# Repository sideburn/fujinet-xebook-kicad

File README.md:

# FN32ROV XEBook KiCad

A KiCad rebuild of the [FujiNet](https://fujinet.online/) FN32ROV WiFi/SIO adapter for
Atari 8-bit computers, adapted for permanent internal mounting inside an XEBook laptop
build.

This project is derived from the FN32ROV-1.7.1 release in
[FujiNetWIFI/fujinet-hardware](https://github.com/FujiNetWIFI/fujinet-hardware), which is
officially certified open source hardware by [OSHWA](https://oshwa.org) (UID
[US000651](https://certification.oshwa.org/us000651.html)). The original design is in
DipTrace; this project is a from-scratch rebuild in KiCad, since DipTrace's binary file
format has no viable automated conversion path into KiCad and this revision changes
enough of the board that preserving the original layout wasn't a goal.

## Status

Work in progress — schematic and PCB layout are still being built out. Not yet fabricated
or tested.

## What's different from FN32ROV-1.7.1

- The two external Atari SIO connectors (SIO plug + SIO receptacle pass-through) are
  replaced with a single low-profile right-angle 12-pin IDC header, hardwired directly to
  the host motherboard rather than daisy-chaining external SIO peripherals.
- The three status LEDs and three tactile buttons move off the PCB onto JST pigtails, so
  they can be panel-mounted separately from the board.
- The onboard microSD socket is retained, with an added parallel breakout header so the
  card can be relocated to an external board later without a further redesign.

Everything else (ESP32-WROVER-E, CP2102N USB-serial bridge, power path, SIO level
shifters) is carried over from the original design.

## Tooling

Built with KiCad 9. `kicad-cli sch erc` / `kicad-cli pcb drc` are used to verify the
design as it's built.

## License

[CERN Open Hardware Licence Version 2 - Strongly Reciprocal](LICENSE) (CERN-OHL-S-2.0),
matching the copyleft, share-alike spirit of the original OSHWA-certified design.

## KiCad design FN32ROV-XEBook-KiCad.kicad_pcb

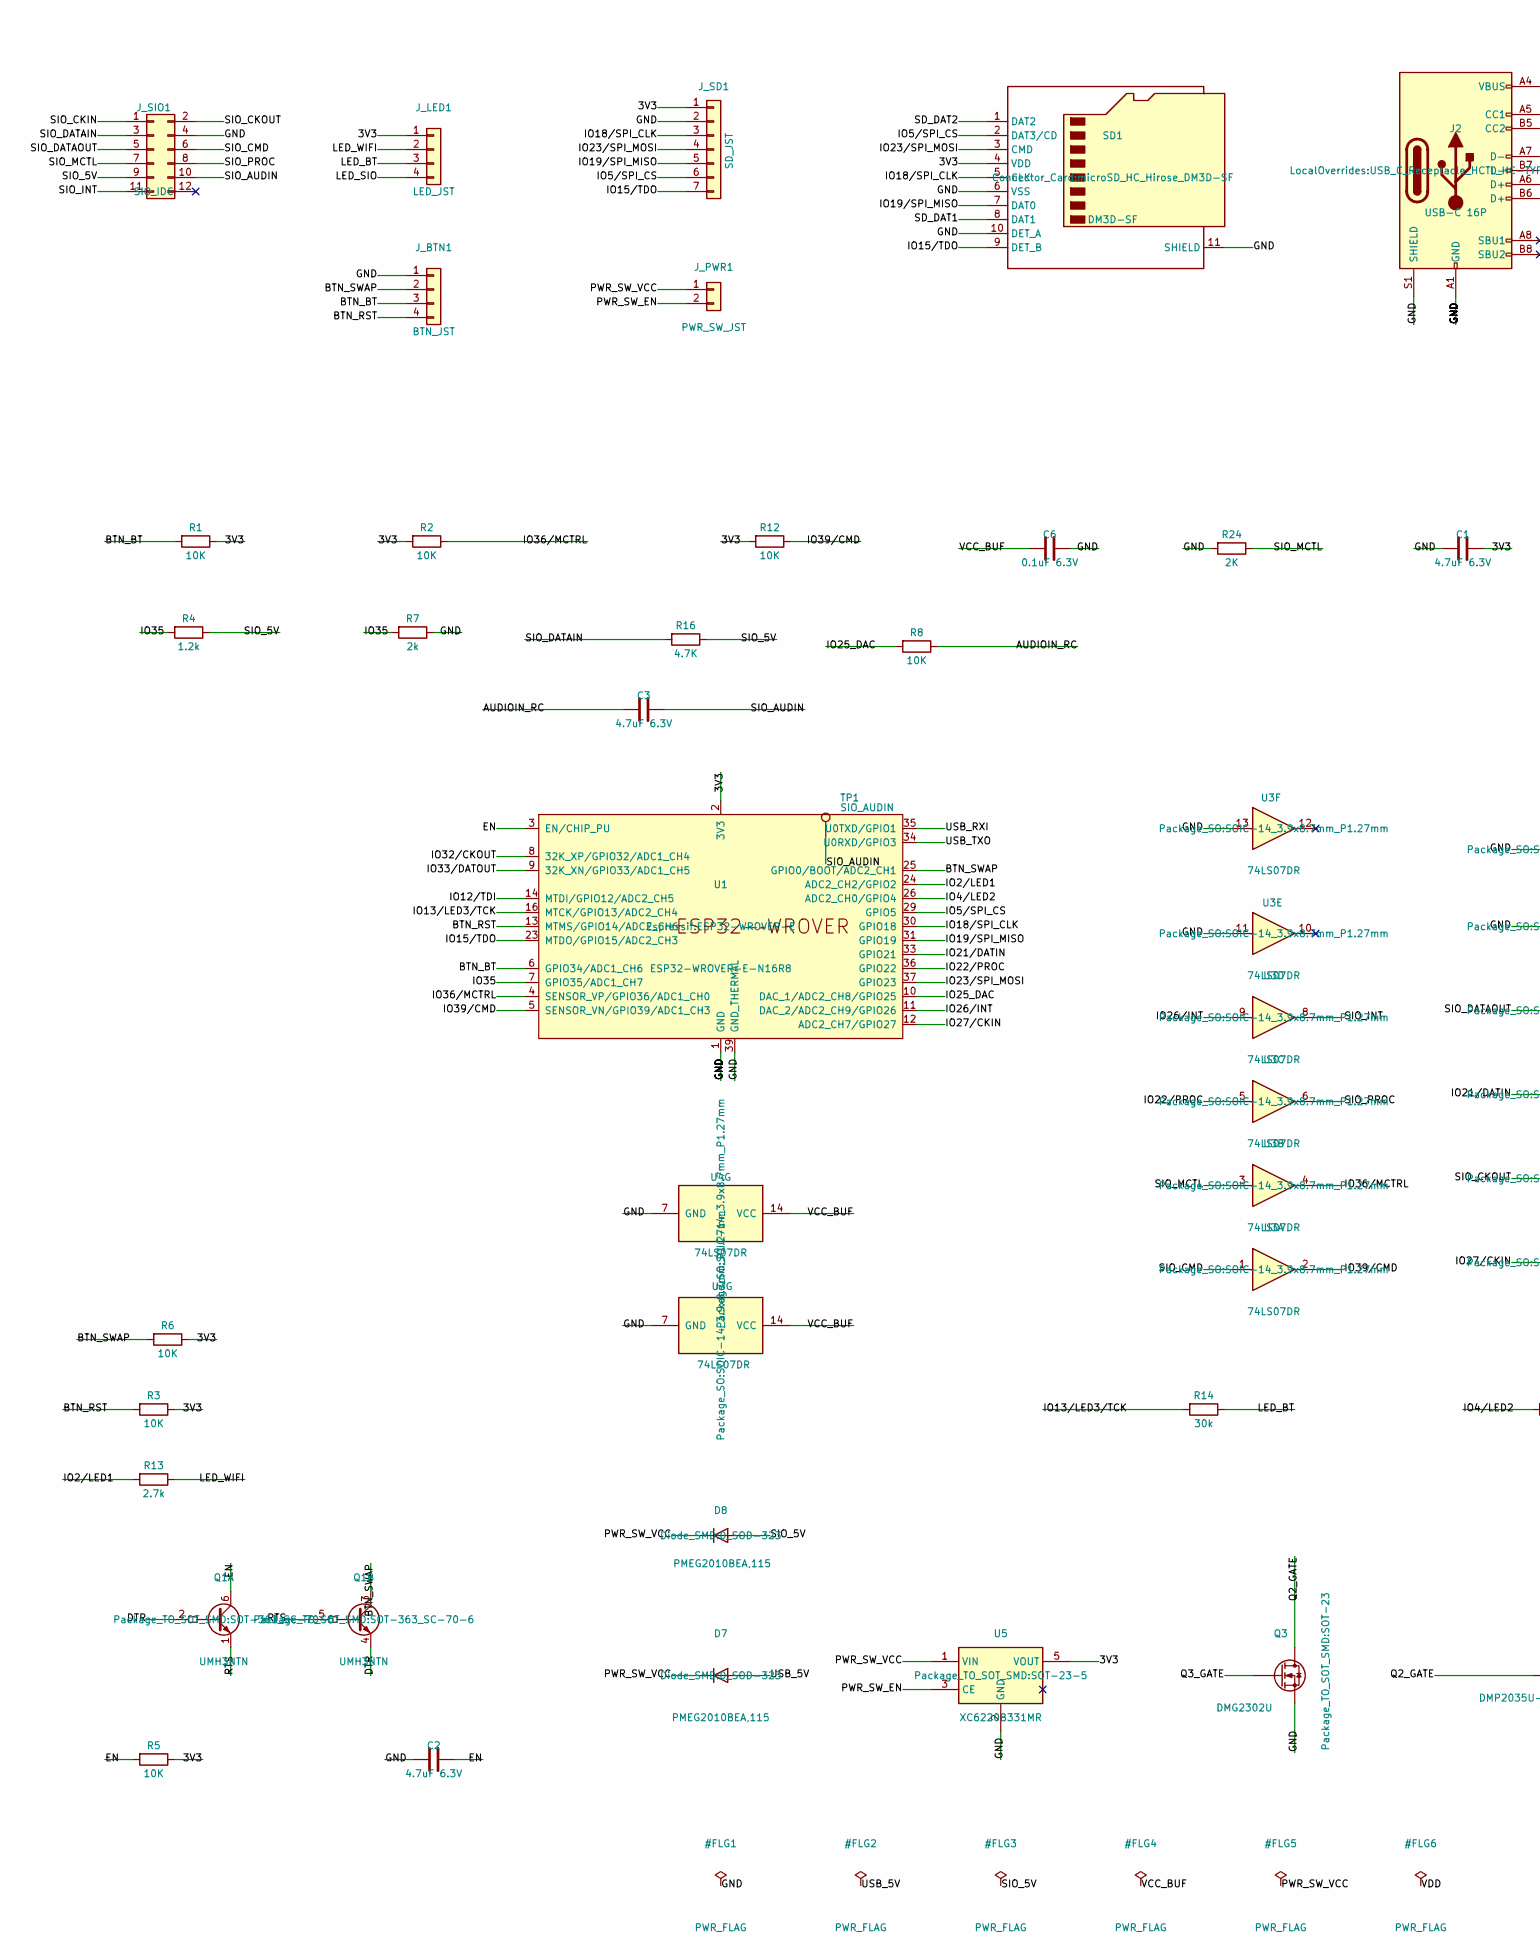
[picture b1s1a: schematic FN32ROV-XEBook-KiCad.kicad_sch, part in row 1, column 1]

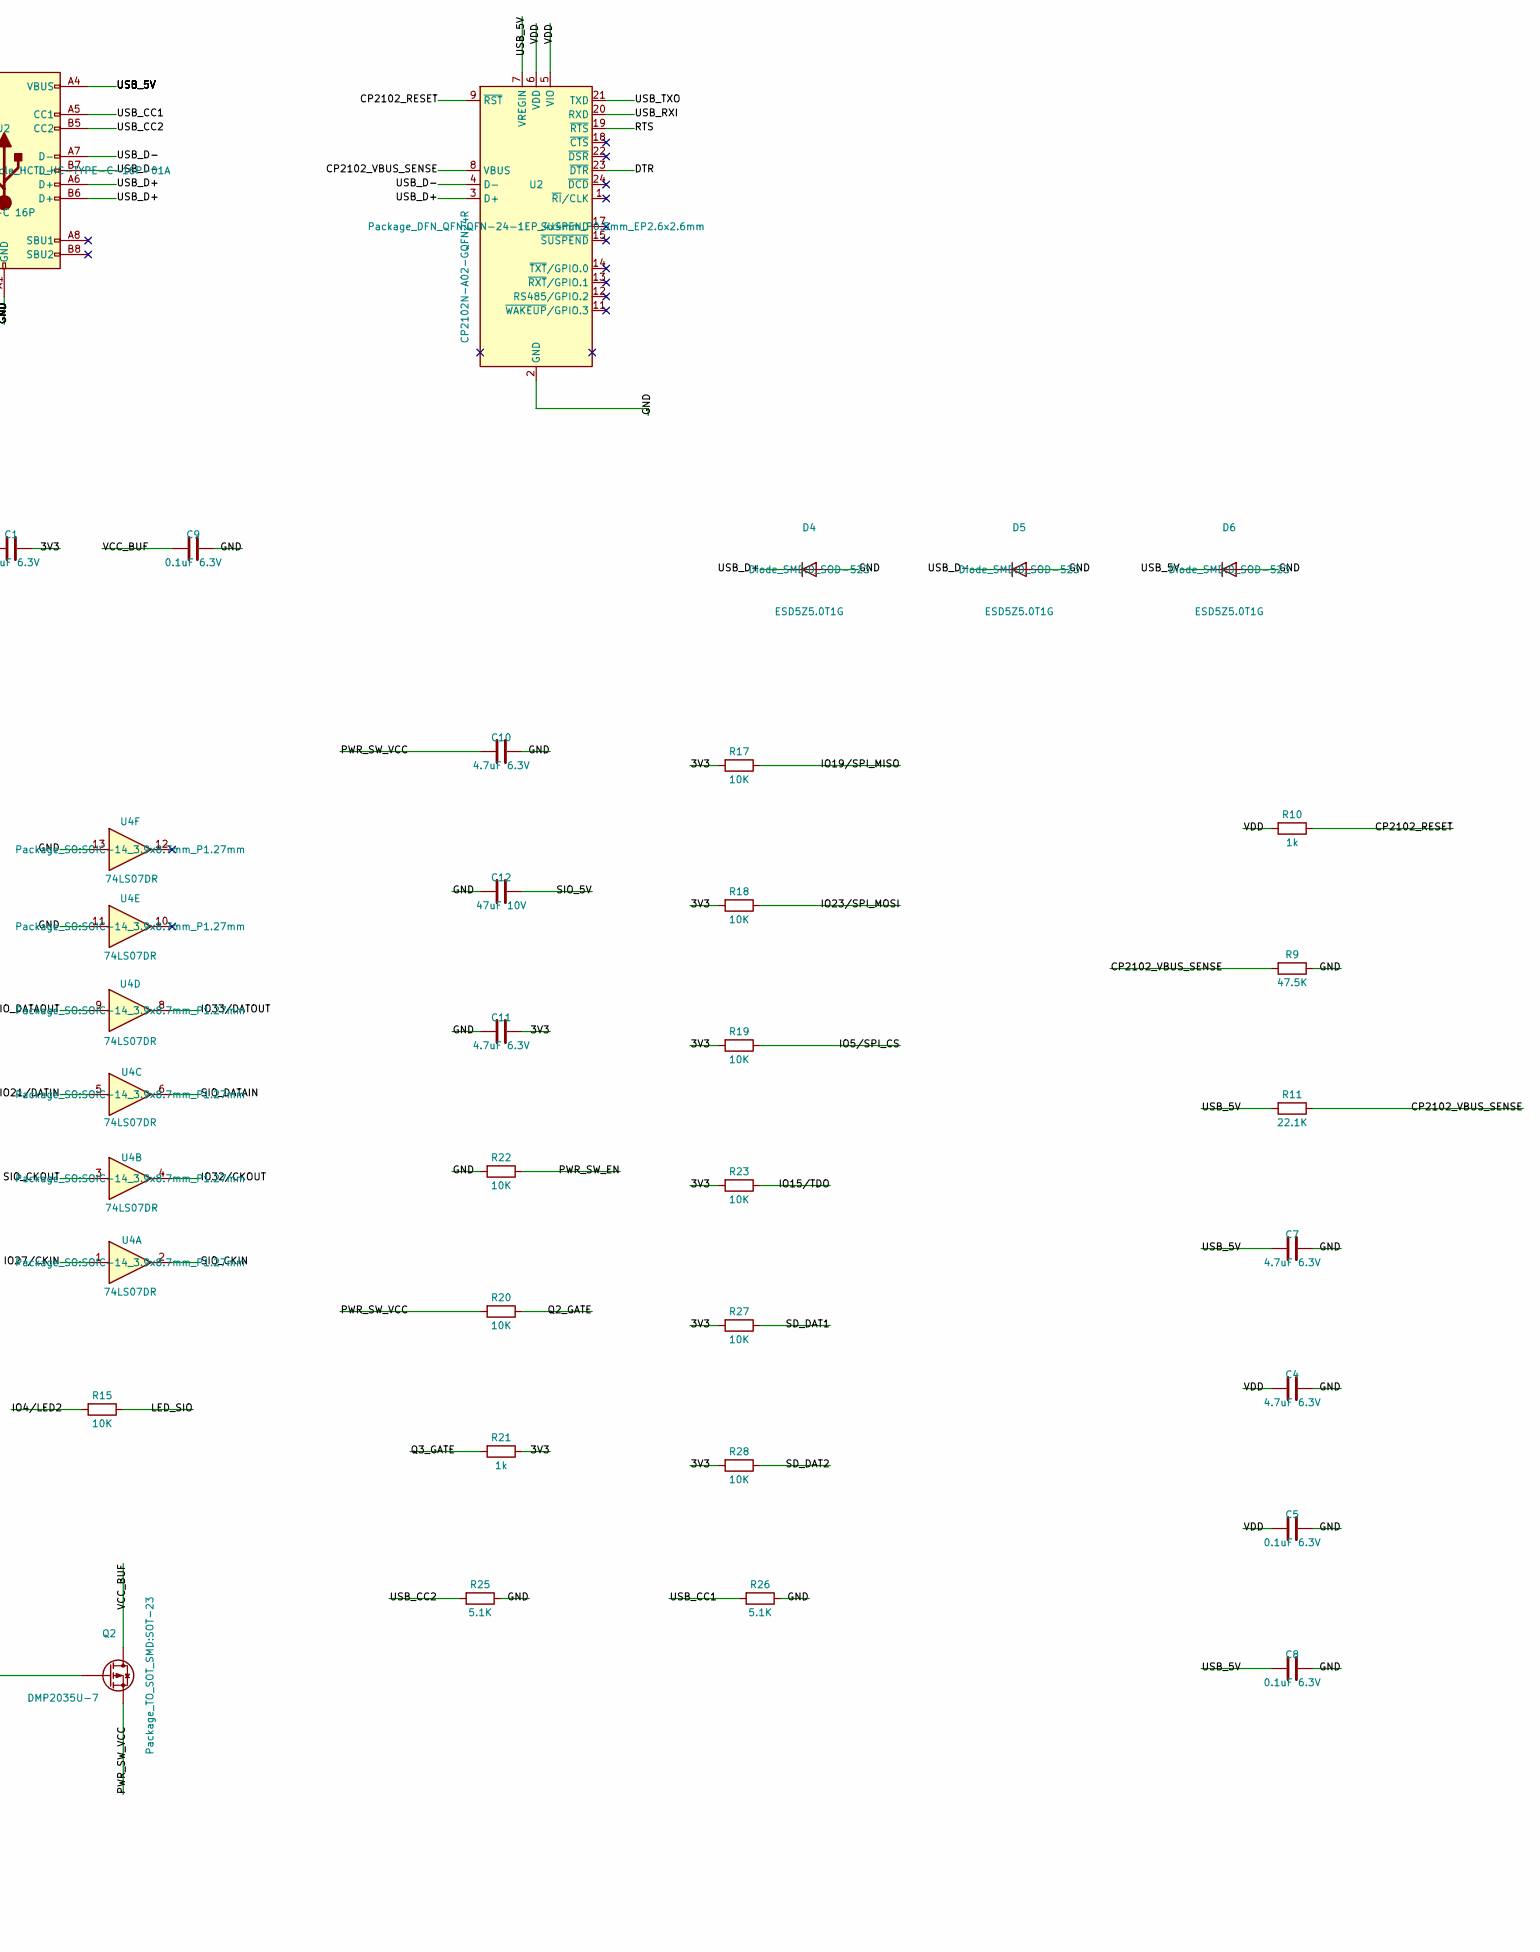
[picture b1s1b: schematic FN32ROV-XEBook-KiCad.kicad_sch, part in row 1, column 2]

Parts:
C1, C2, C3, C4, C7, C10, C11: 4.7uF 6.3V; C_0402_1005Metric
C5, C6, C8, C9: 0.1uF 6.3V; C_0402_1005Metric
C12: 47uF 10V; CP_EIA-7343-31_Kemet-D
D4, D5, D6: ESD5Z5.0T1G; D_SOD-523
D7, D8: PMEG2010BEA,115; D_SOD-323
J2: USB-C 16P; USB_C_Receptacle_HCTL_HC-TYPE-C-16P-01A
J_BTN1: BTN_JST; JST_PH_S4B-PH-K_1x04_P2.00mm_Horizontal
J_LED1: LED_JST; JST_PH_S4B-PH-K_1x04_P2.00mm_Horizontal
J_PWR1: PWR_SW_JST; JST_PH_S2B-PH-K_1x02_P2.00mm_Horizontal
J_SD1: SD_JST; JST_PH_S7B-PH-K_1x07_P2.00mm_Horizontal
J_SIO1: SIO_IDC; IDC-Header_2x06_P2.54mm_Vertical
Q1: UMH3NTN; SOT-363_SC-70-6
Q2: DMP2035U-7; SOT-23
Q3: DMG2302U; SOT-23
R1, R2, R3, R5, R6, R8, R12, R15, R17, R18, R19, R20, R22, R23, R27, R28: 10K; R_0402_1005Metric
R4: 1.2k; R_0402_1005Metric
R7: 2k; R_0402_1005Metric
R9: 47.5K; R_0402_1005Metric
R10, R21: 1k; R_0402_1005Metric
R11: 22.1K; R_0402_1005Metric
R13: 2.7k; R_0402_1005Metric
R14: 30k; R_0402_1005Metric
R16: 4.7K; R_0402_1005Metric
R24: 2K; R_0402_1005Metric
R25, R26: 5.1K; R_0402_1005Metric
SD1: DM3D-SF; microSD_HC_Hirose_DM3D-SF
TP1: SIO_AUDIN; TestPoint_THTPad_D2.0mm_Drill1.0mm
U1: ESP32-WROVER-E-N16R8; ESP32-WROVER-E
U2: CP2102N-A02-GQFN24R; QFN-24-1EP_4x4mm_P0.5mm_EP2.6x2.6mm
U3, U4: 74LS07DR; SOIC-14_3.9x8.7mm_P1.27mm
U5: XC6220B331MR; SOT-23-5

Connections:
/3V3: C1.1, C11.1, J_LED1.1, J_SD1.1, R1.1, R2.2, R3.1, R5.1, R6.1, R12.2, R17.2, R18.2, R19.2, R21.1, R23.2, R27.2, R28.2, SD1.4 (VDD), U1.2 (3V3), U5.5 (VOUT)
/AUDIOIN_RC: C3.2, R8.1
/BTN_BT: J_BTN1.3, R1.2, U1.6 (GPIO34/ADC1_CH6)
/BTN_RST: J_BTN1.4, R3.2, U1.13 (MTMS/GPIO14/ADC2_CH6)
/BTN_SWAP: J_BTN1.2, Q1.3 (C2), R6.2, U1.25 (GPIO0/BOOT/ADC2_CH1)
/CP2102_RESET: R10.1, U2.9 (~RST)
/CP2102_VBUS_SENSE: R9.2, R11.1, U2.8 (VBUS)
/DTR: Q1.2 (B1), Q1.4 (E2), U2.23 (~DTR)
/EN: C2.1, Q1.6 (C1), R5.2, U1.3 (EN/CHIP_PU)
/GND: C1.2, C2.2, C4.1, C5.1, C6.1, C7.1, C8.1, C9.1, C10.1, C11.2, C12.2, D4.2 (A), D5.2 (A), D6.2 (A), J2.A1 (GND), J2.A12 (GND), J2.B1 (GND), J2.B12 (GND), J2.S1 (SHIELD), J_BTN1.1, J_SD1.2, J_SIO1.4, Q3.2 (S), R7.1, R9.1, R22.2, R24.2, R25.1, R26.1, SD1.6 (VSS), SD1.10 (DET_A), SD1.11 (SHIELD), U1.1 (GND), U1.15 (GND), U1.38 (GND), U1.39 (GND_THERMAL), U2.2 (GND), U2.25 (GND), U3.7 (GND), U3.11, U3.13, U4.7 (GND), U4.11, U4.13, U5.2 (GND)
/IO2/LED1: R13.2, U1.24 (ADC2_CH2/GPIO2)
/IO4/LED2: R15.2, U1.26 (ADC2_CH0/GPIO4)
/IO5/SPI_CS: J_SD1.6, R19.1, SD1.2 (DAT3/CD), U1.29 (GPIO5)
/IO12/TDI: U1.14 (MTDI/GPIO12/ADC2_CH5)
/IO13/LED3/TCK: R14.2, U1.16 (MTCK/GPIO13/ADC2_CH4)
/IO15/TDO: J_SD1.7, R23.1, SD1.9 (DET_B), U1.23 (MTDO/GPIO15/ADC2_CH3)
/IO18/SPI_CLK: J_SD1.3, SD1.5 (CLK), U1.30 (GPIO18)
/IO19/SPI_MISO: J_SD1.5, R17.1, SD1.7 (DAT0), U1.31 (GPIO19)
/IO21/DATIN: U1.33 (GPIO21), U4.5
/IO22/PROC: U1.36 (GPIO22), U3.5
/IO23/SPI_MOSI: J_SD1.4, R18.1, SD1.3 (CMD), U1.37 (GPIO23)
/IO25_DAC: R8.2, U1.10 (DAC_1/ADC2_CH8/GPIO25)
/IO26/INT: U1.11 (DAC_2/ADC2_CH9/GPIO26), U3.9
/IO27/CKIN: U1.12 (ADC2_CH7/GPIO27), U4.1
/IO32/CKOUT: U1.8 (32K_XP/GPIO32/ADC1_CH4), U4.4
/IO33/DATOUT: U1.9 (32K_XN/GPIO33/ADC1_CH5), U4.8
/IO35: R4.2, R7.2, U1.7 (GPIO35/ADC1_CH7)
/IO36/MCTRL: R2.1, U1.4 (SENSOR_VP/GPIO36/ADC1_CH0), U3.4
/IO39/CMD: R12.1, U1.5 (SENSOR_VN/GPIO39/ADC1_CH3), U3.2
/LED_BT: J_LED1.3, R14.1
/LED_SIO: J_LED1.4, R15.1
/LED_WIFI: J_LED1.2, R13.1
/PWR_SW_EN: J_PWR1.2, R22.1, U5.3 (CE)
/PWR_SW_VCC: C10.2, D7.1 (K), D8.1 (K), J_PWR1.1, Q2.2 (S), R20.2, U5.1 (VIN)
/Q2_GATE: Q2.1 (G), Q3.3 (D), R20.1
/Q3_GATE: Q3.1 (G), R21.2
/RTS: Q1.1 (E1), Q1.5 (B2), U2.19 (~RTS)
/SD_DAT1: R27.1, SD1.8 (DAT1)
/SD_DAT2: R28.1, SD1.1 (DAT2)
/SIO_5V: C12.1, D8.2 (A), J_SIO1.9, R4.1, R16.1
/SIO_AUDIN: C3.1, J_SIO1.10, TP1.1
/SIO_CKIN: J_SIO1.1, U4.2
/SIO_CKOUT: J_SIO1.2, U4.3
/SIO_CMD: J_SIO1.6, U3.1
/SIO_DATAIN: J_SIO1.3, R16.2, U4.6
/SIO_DATAOUT: J_SIO1.5, U4.9
/SIO_INT: J_SIO1.11, U3.8
/SIO_MCTL: J_SIO1.7, R24.1, U3.3
/SIO_PROC: J_SIO1.8, U3.6
/USB_5V: C7.2, C8.2, D6.1 (K), D7.2 (A), J2.A4 (VBUS), J2.A9 (VBUS), J2.B4 (VBUS), J2.B9 (VBUS), R11.2, U2.7 (VREGIN)
/USB_CC1: J2.A5 (CC1), R26.2
/USB_CC2: J2.B5 (CC2), R25.2
/USB_D+: D4.1 (K), J2.A6 (D+), J2.B6 (D+), U2.3 (D+)
/USB_D-: D5.1 (K), J2.A7 (D-), J2.B7 (D-), U2.4 (D-)
/USB_RXI: U1.35 (U0TXD/GPIO1), U2.20 (RXD)
/USB_TXO: U1.34 (U0RXD/GPIO3), U2.21 (TXD)
/VCC_BUF: C6.2, C9.2, Q2.3 (D), U3.14 (VCC), U4.14 (VCC)
/VDD: C4.2, C5.2, R10.2, U2.5 (VIO), U2.6 (VDD)

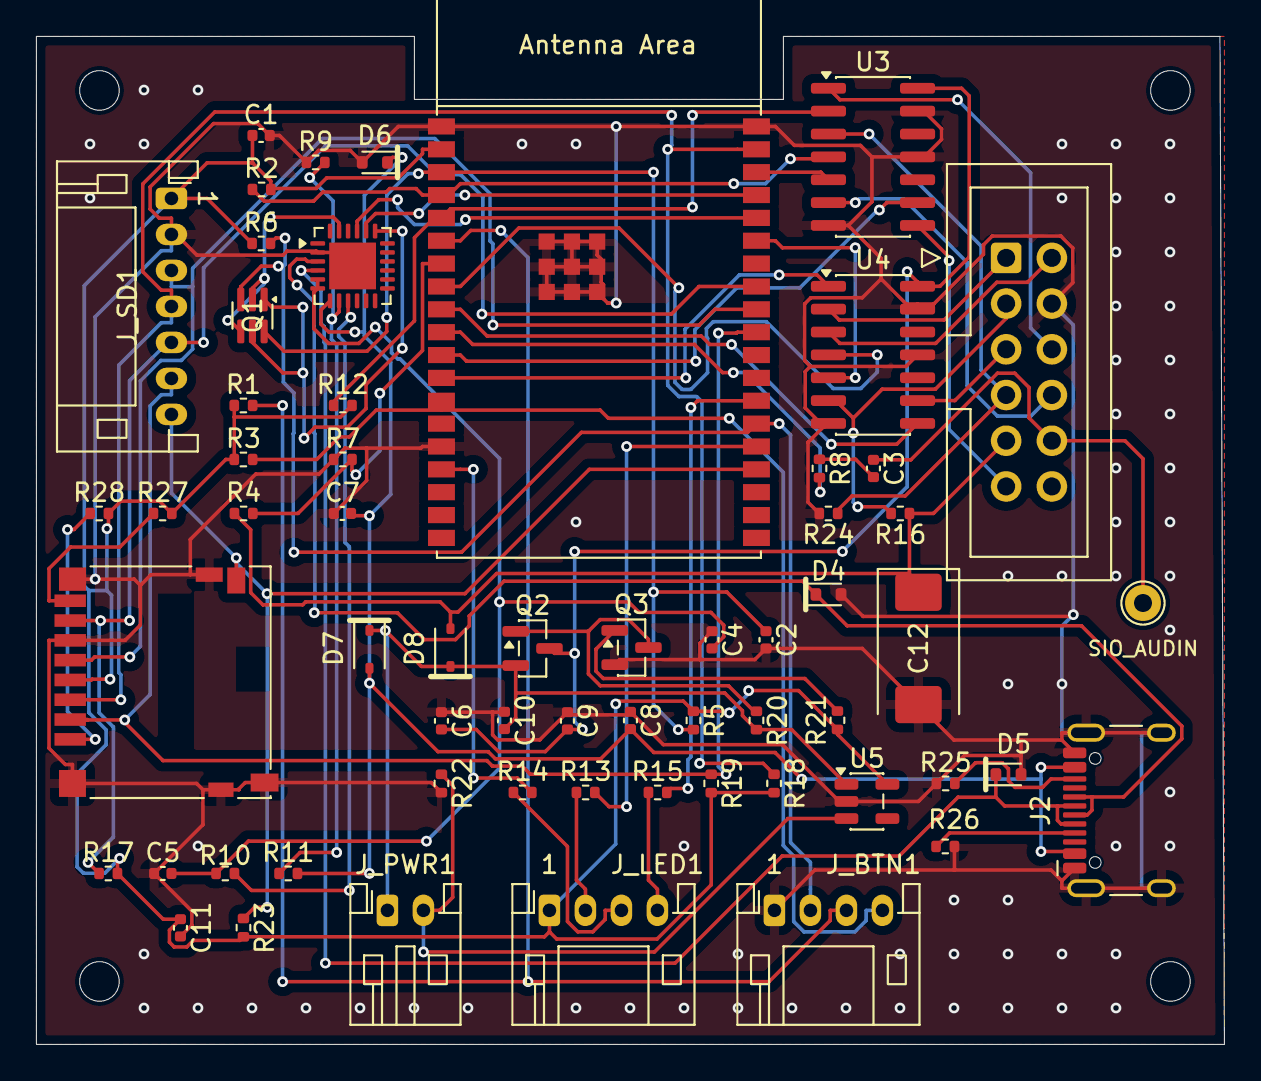
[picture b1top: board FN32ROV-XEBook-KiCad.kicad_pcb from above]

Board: 2 copper layers, 66.0 x 56.0 mm, 65 parts (0 on the bottom side), 57 nets.

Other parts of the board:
MH1, MH2, MH3, MH4: MountingHole_2.2mm_M2

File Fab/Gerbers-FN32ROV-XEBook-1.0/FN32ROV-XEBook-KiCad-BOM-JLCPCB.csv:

Comment,Designator,Footprint,LCSC Part #
4.7uF 6.3V,C1,Capacitor_SMD:C_0402_1005Metric,C23733
4.7uF 6.3V,C2,Capacitor_SMD:C_0402_1005Metric,C23733
4.7uF 6.3V,C3,Capacitor_SMD:C_0402_1005Metric,C23733
4.7uF 6.3V,C4,Capacitor_SMD:C_0402_1005Metric,C23733
4.7uF 6.3V,C7,Capacitor_SMD:C_0402_1005Metric,C23733
4.7uF 6.3V,C10,Capacitor_SMD:C_0402_1005Metric,C23733
4.7uF 6.3V,C11,Capacitor_SMD:C_0402_1005Metric,C23733
0.1uF 6.3V,C5,Capacitor_SMD:C_0402_1005Metric,C1525
0.1uF 6.3V,C6,Capacitor_SMD:C_0402_1005Metric,C1525
0.1uF 6.3V,C8,Capacitor_SMD:C_0402_1005Metric,C1525
0.1uF 6.3V,C9,Capacitor_SMD:C_0402_1005Metric,C1525
47uF 10V,C12,Capacitor_Tantalum_SMD:CP_EIA-7343-31_Kemet-D,C503930
ESD5Z5.0T1G,D4,Diode_SMD:D_SOD-523,C2879719
ESD5Z5.0T1G,D5,Diode_SMD:D_SOD-523,C2879719
ESD5Z5.0T1G,D6,Diode_SMD:D_SOD-523,C2879719
"PMEG2010BEA,115",D7,Diode_SMD:D_SOD-323,C455041
"PMEG2010BEA,115",D8,Diode_SMD:D_SOD-323,C455041
USB-C 16P,J2,LocalOverrides:USB_C_Receptacle_HCTL_HC-TYPE-C-16P-01A,C2894897
BTN_JST,J_BTN1,Connector_JST:JST_PH_S4B-PH-K_1x04_P2.00mm_Horizontal,C265452
LED_JST,J_LED1,Connector_JST:JST_PH_S4B-PH-K_1x04_P2.00mm_Horizontal,C265452
PWR_SW_JST,J_PWR1,Connector_JST:JST_PH_S2B-PH-K_1x02_P2.00mm_Horizontal,C265016
SD_JST,J_SD1,Connector_JST:JST_PH_S7B-PH-K_1x07_P2.00mm_Horizontal,C157917
SIO_IDC,J_SIO1,LocalOverrides:IDC-Header_2x06_P2.54mm_Latch_Horizontal,
UMH3NTN,Q1,Package_TO_SOT_SMD:SOT-363_SC-70-6,C123008
DMP2035U-7,Q2,Package_TO_SOT_SMD:SOT-23,C110499
DMG2302U,Q3,Package_TO_SOT_SMD:SOT-23,C96613
10K,R1,Resistor_SMD:R_0402_1005Metric,C25744
10K,R2,Resistor_SMD:R_0402_1005Metric,C25744
10K,R3,Resistor_SMD:R_0402_1005Metric,C25744
10K,R5,Resistor_SMD:R_0402_1005Metric,C25744
10K,R6,Resistor_SMD:R_0402_1005Metric,C25744
10K,R8,Resistor_SMD:R_0402_1005Metric,C25744
10K,R12,Resistor_SMD:R_0402_1005Metric,C25744
10K,R17,Resistor_SMD:R_0402_1005Metric,C25744
10K,R18,Resistor_SMD:R_0402_1005Metric,C25744
10K,R19,Resistor_SMD:R_0402_1005Metric,C25744
10K,R20,Resistor_SMD:R_0402_1005Metric,C25744
10K,R22,Resistor_SMD:R_0402_1005Metric,C25744
10K,R23,Resistor_SMD:R_0402_1005Metric,C25744
10K,R27,Resistor_SMD:R_0402_1005Metric,C25744
10K,R28,Resistor_SMD:R_0402_1005Metric,C25744
1.2k,R4,Resistor_SMD:R_0402_1005Metric,C25862
1.2k,R15,Resistor_SMD:R_0402_1005Metric,C25862
2k,R7,Resistor_SMD:R_0402_1005Metric,C413086
47.5K,R9,Resistor_SMD:R_0402_1005Metric,C25896
1k,R10,Resistor_SMD:R_0402_1005Metric,C11702
2.7k,R13,Resistor_SMD:R_0402_1005Metric,C413089
1k,R14,Resistor_SMD:R_0402_1005Metric,C11702
1k,R21,Resistor_SMD:R_0402_1005Metric,C11702
22.1K,R11,Resistor_SMD:R_0402_1005Metric,C163478
4.7K,R16,Resistor_SMD:R_0402_1005Metric,C413001
2K,R24,Resistor_SMD:R_0402_1005Metric,C413086
5.1K,R25,Resistor_SMD:R_0402_1005Metric,C25905
5.1K,R26,Resistor_SMD:R_0402_1005Metric,C25905
DM3D-SF,SD1,Connector_Card:microSD_HC_Hirose_DM3D-SF,C719027
ESP32-WROVER-IE-N16R8,U1,Espressif:ESP32-WROVER-E,C701352
CP2102N-A02-GQFN24R,U2,Package_DFN_QFN:QFN-24-1EP_4x4mm_P0.5mm_EP2.6x2.6mm,C969151
74LS07DR,U3,Package_SO:SOIC-14_3.9x8.7mm_P1.27mm,C371970
74LS07DR,U4,Package_SO:SOIC-14_3.9x8.7mm_P1.27mm,C371970
XC6220B331MR,U5,Package_TO_SOT_SMD:SOT-23-5,C3040644
